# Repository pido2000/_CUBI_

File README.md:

### Description

Simple open source bluetooth controlled wheeled robot. Mechanical design, electronics and software designs available on this repo.
Remy F. used @Gregwar's Holo as a starting point.

The initial design is a cube like robot :

https://www.youtube.com/watch?v=2ZDV0_4vD0g

https://www.youtube.com/watch?v=TOusHRbKWQg

A second design was also made to play around cart-poling:

https://www.youtube.com/watch?v=Ubej95gH9Gs

TODO:

- Add Julien's O. designs and events

- Add Julien's A. and Jérémy's designs and event (cap science)

### Simulation
Some simulation stuff (simple kinematic control, inverted pendulum tests) is available in Python here :
https://bitbucket.org/RemiFabre/cubi/src/master/simulation/

0) Installation
You'll need Python (any version should work) and pygame
```
pip install pygame
```

1) Simple control of a wheeled robot (click around)
```
python main.py
```
https://www.youtube.com/watch?v=O8ZoUAvGYmE

2) Inverted pendulum (cart-pole) simulation
```
python cart_pole.py
```
https://www.youtube.com/watch?v=xhEcLnnj7fg

### How to make it work
You'll have to install the arm cross-compilation tools. On debian-like distributions,
you can get it with:

```
    sudo aptitude install build-essential git-core dfu-util openocd python \
        python-serial binutils-arm-none-eabi gcc-arm-none-eabi libstdc++-arm-none-eabi-newlib
```
If you're running an Ubuntu 14.04 or older, you might need to install the libstdc++-arm-none-eabi-newlib packet by hand. Download link :
http://ftp.de.debian.org/debian/pool/main/libs/libstdc++-arm-none-eabi/libstdc++-arm-none-eabi-newlib_4.8.3-9+4_all.deb

Command (if a conflict rises, you can add --force-overwrite to the following line):
```
	sudo dpkg -i libstdc++-arm-none-eabi-newlib_4.8.3-9+4_all.deb
```
Go to the `firmware/src` directory and edit the `Makefile` to set the appropriate
`BOARD` variable, targetting your servo.

You can then run:

```
make
```

Use an USB cable to connect your pc with the robot's board

```
make install
```
### Bluetooth

First you need to set the name and the pasword using a cable.

```
cu -l /dev/ttyACM0
btconf <name> <pswrd>
```

Then, you can control the robot without the need of a cable. The most straight-forward way is to download the "Metabot" app from Google Play. Once on the app you can scan for devices, find your robot and pair it with your phone.

If you want to pair your PC with your robot, one method is as follows (Ubuntu).

Uninstall modemmanager (not needed but causes some issues)

```
    sudo apt-get purge modemmanager
```

Scan for bluetooth devices and save the adress (e.g. 98:D3:37:90:ED:D6) of your robot. For example, we use blueman-manager :

```
    sudo apt-get install blueman
    sudo blueman-manager
```

Assign a serial port to the connection. You can do that on the graphical interface of blueman-manager but doing it directly with rfcomm seems more robust :

```
    sudo rfcomm bind /dev/rfcomm0 98:D3:37:90:ED:D6
```

Now you can access the remote terminal on the robot with :

```
    cu -l /dev/rfcomm0
```

You might have permission access issues. Make sure you're in the dialout group or go bonkers :

```
    sudo chmod 777 /dev/rfcomm0 && cu -l /dev/rfcomm0
```

### Electronics

A board was made with all integrated components in order to drop fabrication cost. 

Top

Bottom

### Mecanics

Cubi's design is simple. It consist of a squared box. The majority was made in MDF.

Visual from Onshape

The design is transposed in the following svg file.

We also enjoyed the look of PMMA.

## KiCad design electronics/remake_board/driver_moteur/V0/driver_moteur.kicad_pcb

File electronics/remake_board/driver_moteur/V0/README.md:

### Description

Le projet "driver_moteur" est un prototype visant à séparer la carte électronique globale en 2 modules distincts pour faciliter le placement de cette carte à l'interieur du robot.
Pour une approche plus proche du Plug-And-Play, on voudrait aussi implanter des connecteurs magnétiques (Pogo pins) permettant de lier les 2 cartes facilement.

Un premier module s'occuperait de la gestion d'alimentation globale, avec le driver des moteurs et du régulateur 9V vers 5V.
Le deuxième module utiliserait le reste des composants traitant les données, avec le µC, le module Bluetooth, le buzzer et la centrale inertielle.

Ce projet est une piste d'amélioration (et d'optimisation) de la carte électronique.

### Inconvénient projet

Si l'on veut séparer la carte en 2 modules, cela implique un coût supplémentaire dû à la fabrication de 2 cartes distinctes + aux rajouts de connecteurs magnétiques liant celles-ci.

### Avantage projet

On peut connecter directement le module de gestion d'alim aux moteurs sans câbles et "plugger" l'autre module directement.
En effet, on peut difficilement créer une carte globale qui respecte les conditions de placement des connecteurs moteurs ET simplifie la mécanique du robot. 

### Notes à part

Nous n'avons créé qu'une seule version qui n'a pas encore été testée.
De plus, certaines soudures sont difficilement réalisables si l'on veut fabriquer le module soi-même.

Comme l'on possède 2 connecteurs Pogo de 8 broches, on a rajouté 4 pins disponibles pour commander des Leds supplémentaires.
Mais on peut tout à fait n'utiliser que 12 broches au total pour une version ultérieure du module.

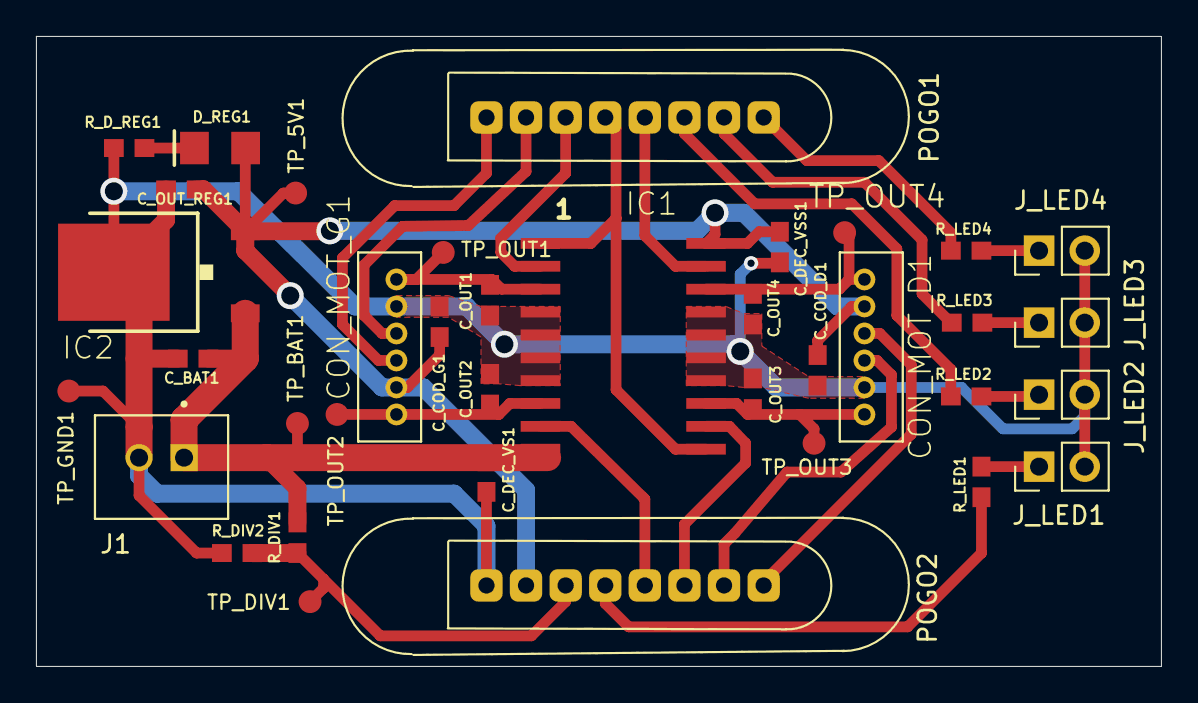
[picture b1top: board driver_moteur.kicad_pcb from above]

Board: 2 copper layers, 62.5 x 35.0 mm, 37 parts (0 on the bottom side), 26 nets.

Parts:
CON_MOT_D1: B6B-ZR
CON_MOT_G1: B6B-ZR
C_BAT1: 0.1µF; 0603
C_COD_D1: 22nF; 0603
C_COD_G1: 22nF; 0603
C_DEC_VS1: 1µF; 0603
C_DEC_VSS1: 0.1µF; 0603
C_OUT1, C_OUT2, C_OUT3, C_OUT4: 22nF; 0603
C_OUT_REG1: 0.1µF; 0603
D_REG1: LED-FKIT-1206; FKIT-LED-1206
IC1: L293DD; SO20
IC2: MC78M; DPACK_3
J1: B2B-XH-A(LF)(SN); JST_B2B-XH-A(LF)(SN)
J_LED1, J_LED2, J_LED3, J_LED4: Conn_01x02_Female; PinHeader_1x02_P2.54mm_Vertical
POGO1, POGO2: Pogo_magn_8pin; CONN_pogopin_8_female
R_DIV1: 60k; 0603
R_DIV2: 30k; 0603
R_D_REG1: 240; 0603
R_LED1, R_LED2, R_LED3, R_LED4: ?; 0603
TP_5V1: PTR1B1,27; B1,27
TP_BAT1: PTR1B1,27; B1,27
TP_DIV1: PTR1B1,27; B1,27
TP_GND1: PTR1B1,27; B1,27
TP_OUT1, TP_OUT2, TP_OUT3, TP_OUT4: PTR1B1,27; B1,27

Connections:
/3_AIN: POGO2.6, R_DIV1.1, R_DIV2.1, TP_DIV1.TP
/5V: CON_MOT_D1.2, CON_MOT_G1.2, C_COD_D1.1, C_COD_G1.1, C_DEC_VSS1.1, C_OUT_REG1.1, D_REG1.A, IC1.20, IC2.3, POGO2.7, TP_5V1.TP
/9V: C_BAT1.1, C_DEC_VS1.1, IC1.10, IC2.1, J1.1, R_DIV1.2, TP_BAT1.TP
/COD_D1: CON_MOT_D1.4, POGO2.2
/COD_D2: CON_MOT_D1.3, POGO2.1
/COD_G1: CON_MOT_G1.4, POGO1.7
/COD_G2: CON_MOT_G1.3, POGO1.8
/EN_MOT: IC1.1, IC1.11, POGO1.5
/IN_MOT_D1: IC1.12, POGO2.3
/IN_MOT_D2: IC1.19, POGO1.4
/IN_MOT_G1: IC1.2, POGO1.6
/IN_MOT_G2: IC1.9, POGO2.4
/MOT_D1: CON_MOT_D1.6, C_OUT3.1, IC1.13, TP_OUT3.TP
/MOT_D2: CON_MOT_D1.1, C_OUT4.1, IC1.18, TP_OUT4.TP
/MOT_G1: CON_MOT_G1.6, C_OUT1.1, IC1.3, TP_OUT1.TP
/MOT_G2: CON_MOT_G1.1, C_OUT2.1, IC1.8, TP_OUT2.TP
GND: CON_MOT_D1.5, CON_MOT_G1.5, C_BAT1.2, C_COD_D1.2, C_COD_G1.2, C_DEC_VS1.2, C_DEC_VSS1.2, C_OUT1.2, C_OUT2.2, C_OUT3.2, C_OUT4.2, C_OUT_REG1.2, IC1.4, IC1.5, IC1.6, IC1.7, IC1.14, IC1.15, IC1.16, IC1.17, IC2.4, J1.2, J_LED1.2, J_LED2.2, J_LED3.2, J_LED4.2, POGO2.8, R_DIV2.2, R_D_REG1.1, TP_GND1.TP
unnamed: D_REG1.C, R_D_REG1.2
unnamed: J_LED1.1, R_LED1.2
unnamed: J_LED2.1, R_LED2.2
unnamed: J_LED3.1, R_LED3.2
unnamed: J_LED4.1, R_LED4.2
unnamed: POGO1.1, R_LED4.1
unnamed: POGO1.2, R_LED3.1
unnamed: POGO1.3, R_LED2.1
unnamed: POGO2.5, R_LED1.1

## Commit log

2021-06-30 Initial files
2021-06-30 Adding Maple library
2021-06-30 Adding current CUBI_BOX layout
2021-06-30 New organisatin of docs
2021-06-30 Move electronics
2021-06-30 Update electronics & mechanics
2021-07-01 README for elec
2021-07-01 Cubi's box .svg
2021-07-01 change src
2021-07-06 uploading pictures
2021-07-06 pictures uploaded
2021-07-06 uploading pictures [meca][elec]
2021-07-06 Updating README (pictures&bluetooth related info)
2021-07-06 Adding README for driveur_moteur project
2021-07-09 Correction README du driver moteur, partie elec
2021-07-09 Update README, electronics part
2021-08-02 remove unwanted filed
